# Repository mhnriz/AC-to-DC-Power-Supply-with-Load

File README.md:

EFB1031 Electrical Circuit Analysis Lab May 2024

DC power supply with a fixed 15 V output using a full-wave rectifier (center-tap).

Load: Mega 2560 Arduino with RC255 RFID and Buzzer.

RC522 RFID Module and Buzzer Connection Diagram
|RC522 RFID Pin|Arduino Pin| 
| ------------- | ------------- |
|VCC|N/A|
|GND|GND|
|SDA|53|
|SCK|52|
|MOSI|51|
|MISO|50|
|RST|5|
|IRQ|N/A (optional)|

Buzzer Connection
|Buzzer Pin|Arduino Pin|Resistor (Ω)|
| ------------- | ------------- | ------------- |
|VCC|5V (optional)|N/A|
|GND|GND|N/A|
|I/O|8|N/A|

|RGB LED Pin|Arduino Pin|Resistor (Ω)|
| ------------- | ------------- | ------------- |
|GND|GND|N/A|
|Red pin|9|220Ω|
|Green pin|10|220Ω|
|Blue pin|11|220Ω|

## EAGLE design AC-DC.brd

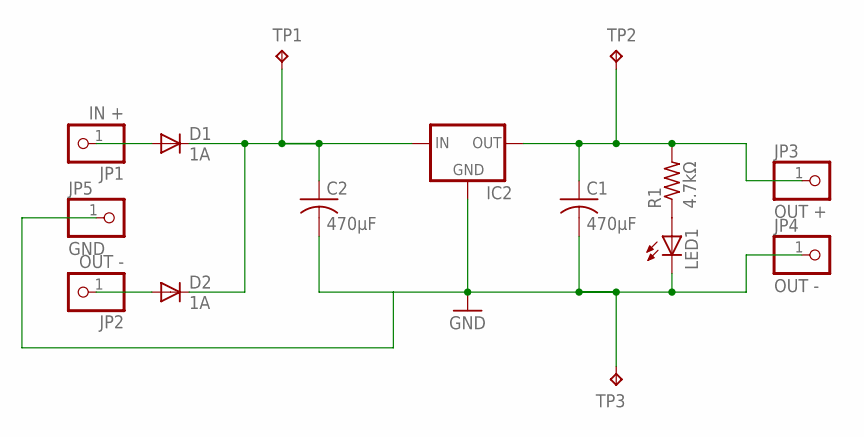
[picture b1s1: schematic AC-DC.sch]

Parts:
C1, C2: 470μF; C075-032X103
D1, D2: 1A; DO41-10
IC2: 78XXS
JP1: IN +; 1X01
JP2, JP4: OUT -; 1X01
JP3: OUT +; 1X01
JP5: GND; 1X01
LED1: LED10MM
R1: 4.7kΩ; 0207/10
TP1, TP2, TP3: TPB1,27; B1,27

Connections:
GND: C1.2, C2.2, IC2.GND, JP4.1, JP5.1, LED1.K (C), TP3.TP
unnamed: C2.1, D1.C, D2.C, IC2.IN, TP1.TP
unnamed: C1.1, IC2.OUT, JP3.1, R1.2, TP2.TP
unnamed: LED1.A, R1.1
unnamed: D1.A, JP1.1
unnamed: D2.A, JP2.1

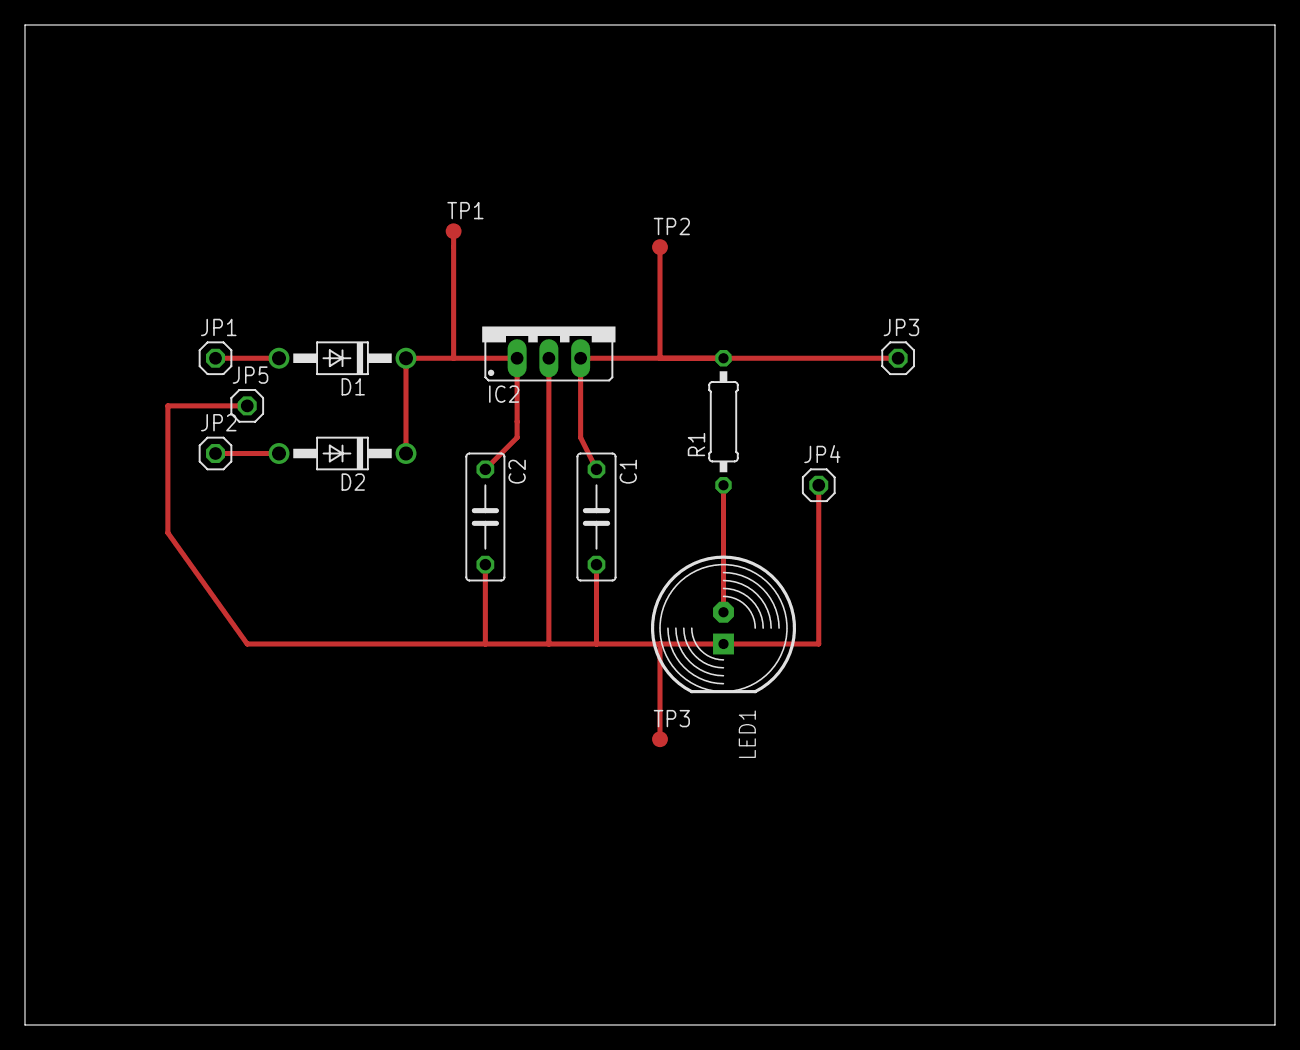
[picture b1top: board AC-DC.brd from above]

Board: 2 copper layers, 100.0 x 80.0 mm, 15 parts (0 on the bottom side), 6 nets.

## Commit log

2024-07-19 Add files via upload
    PCB board
